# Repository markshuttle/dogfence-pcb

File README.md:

# Dog Fence Indicator & Surge Protection System

**Draft hardware revision: 1.2.1-dev. Reviewed baseline: 1.1.0. File-verified prototype artifacts are authorized; production and field release remain on hold. No upload or order is authorized.**

This repository documents a 4 km DogWatch SmartFence boundary with local DC fault
indicators and GDT surge paths. The implemented 16-part hybrid includes series
indicator branches and negative-voltage output shunts; it is not a qualified
lightning-protection design or completed hardware test report.

[REMEDIATION](REMEDIATION.md) owns the agreed requirements, issue decisions and
revision-specific results. [BOM.csv](pcb/BOM.csv) and the synchronized CAD/local
libraries own PCB population; [ASSEMBLY](pcb/ASSEMBLY.md#reviewed-components)
explains assembly applicability. [MATERIALS](MATERIALS.md#resistor-procurement-and-history)
preserves purchases, cancellations and allocations. A production pre-order is
not an implemented substitution, and prototype results do not qualify another part.

Use the working schematic, PCB, settings/rules and libraries under `pcb/`, not
generated `build/`, backups or `tmp/` copies, as design sources. File verification
does not close the [engineering holds and release gates](REMEDIATION.md#release-gates).

## 1. Deployment Baseline

| Item | Agreed requirement |
| :--- | :--- |
| Stations | **41**, at 0, 100, ..., 4000 m, covering 40 diagnostic spans. The 0 km and 4 km stations are separate boards at the shed. |
| Station types | **36 standard + 5 earth-connected**, retaining earth-connected locations at 0, 1000, 2000, 3000, and 4000 m. Five locations do not imply five independent electrodes. |
| Field equipment | One identical, fully populated board and two external LEDs per station. [MATERIALS](MATERIALS.md#1-station-inventory) owns total requirements, purchases and shortfalls. |
| Initial order | **Five fully assembled JLCPCB boards**, all required SMT and THT parts fitted. No field soldering. Prototype allocation and later production/spares are separate decisions. |
| Fabrication | Readily available **FR-4, two layers, 2 oz / 70 micrometres copper on both F.Cu and B.Cu, ENIG, nominal 1.6 mm finished thickness**. Green soldermask is the quote default, not a new performance qualification. No imposed high-Tg laminate, gold thickness upgrade, or filled-via process. |
| Enclosure | WISKA COMBI 308 with Essentra LCBSBM-6-01A-RT supports and WISKA **OneGel**, subject to assembled fit and process acceptance. Raised installation, not continuous submersion. |
| TEST duty | Nominal 36 V DC, usually one to two hours. **Continuous-safe normal TEST** is required for accidental extended operation; a timer is not the baseline safeguard. Fault/surge safety needs separate evidence. |
| Visibility | ON/OFF distinguishable at **5 m in full daylight**, at the final minimum field current and actual viewing angles. |

[MATERIALS](MATERIALS.md#assembly-and-quantity-allocation) separates field needs
from prototype consumption, the retained reference and spares. A five-board
prototype order is not five proven field spares.

## 2. Operation And Fault Localization

### Hub Contact Matrix

Both physical cable ends return to the shed. The full
[functional matrix](INSTALL.md#functional-matrix) uses **six independent ends**:
TEST feeds Start A/C positive and Start B negative, leaving End A/B/C individually
isolated. Required ties belong on source-side contacts only. No permanent End A/C
strap, opposite-end B return or dual-B negative return is permitted; those
connections defeat the agreed indication. OFF isolates all six ends at the hub,
but is not demonstrated lightning or maintenance isolation.

Follow [INSTALL's switch/source controls](INSTALL.md#switch-and-supply). Exact
switch configuration, DC suitability and global transfer require approval before
physical terminal assignment; extra poles remain unassigned. No direction
selector, automatic core classification or automatic return to RUN is required.

**TEST and OFF disable RF containment.** Provide clear RUN/OFF/TEST and fence-inactive labeling/indication, independent animal containment during testing, and an explicit operator return to RUN. See [INSTALL.md](INSTALL.md) for the controlled operating instructions and [RISKS.md](RISKS.md) for fault/earthing limitations.

### Indication For A Clean Cut

Use [INSTALL's clean-cut truth table](INSTALL.md#clean-cut-indications) for one
cut site with healthy indicators/GDTs and no additional inter-core shorts. The
first applicable state transition identifies the adjacent 100 m span, including
3900-4000 m; exact broken-core classification is not required. For multiple sites,
[repair and repeat TEST](INSTALL.md#repair-and-retest). Mixed open/short faults or
failed indicators/GDTs need separate troubleshooting; not every dark LED proves a cut.

### Station Connections

Three **WAGO 221-613** three-way splices maintain A/B/C cable continuity and provide short 2.5 mm^2 taps to `J_IN`. Normal perimeter current does **not** pass through every PCB's rails; each PCB draws its local indicator current. Surge current through a board is a different design case.

The [implemented circuit](pcb/ELECTRICAL.md#1-implemented-model) has separate
A-to-B and C-to-B one-way indicator branches. D3/D4 are output shunts after
D1/D2, not additional series parts. GDT paths join the core pairs and the separate
EARTH bus. Standard boards retain all parts but leave external `J_EARTH` unwired;
earth-connected stations follow the accepted site design.

RUN parallels the three cores at each transmitter end. The electrical record
preserves the historical parallel-resistance comparison, not RF compatibility
proof. Actual imbalance, faults, capacitance and earth coupling require checks
with the transmitter and receiver; the boards are not demonstrated RF-invisible.

## 3. Electrical Limits And Open Protection Work

Use [ELECTRICAL's named historical comparisons](pcb/ELECTRICAL.md#2-calculated-results)
and [DESIGN_BOUNDS](pcb/DESIGN_BOUNDS.md) for the current population's
cable/tolerance, leakage, power and fault screens. They are conditional models,
not measurements, enforced source limits, an exhaustive brightness minimum or
thermal qualification. The source/test commands and assumptions travel with those
records; do not copy retired-part values into current operating limits.

- Use **one TEST supply and one disconnected spare**, never interconnected
  supplies. Verify the actual unit and qualified settings under
  [INSTALL](INSTALL.md#switch-and-supply); a larger PSU does not coordinate faults.
- Negative shunts are not forward pulse-current regulators or reversed-lead
  immunity. Reverse recovery is not forward-clamp response. Ordinary RF,
  switching and nearby-lightning behavior remain unqualified.
- Cable-limited faults may not clear the fuse promptly. Powered-GDT recovery is
  unresolved, not an observed latched failure; conditional load lines do not
  predict extinction. Indicator resistors/shunts do not protect upstream GDT paths.
- Resistor wattage and SMT construction do not prove cool OneGel operation.
  Manufacturer mounting/rating transfer and actual chip/pad/PCB/material-interface
  temperatures require separate qualification; retired-part pulse/thermal data do
  not transfer. Continuous-safe normal TEST remains mandatory, without a timer.
- DC sparkover is not transient clamp voltage. Component impulse ratings,
  paralleled pins and heavy copper do not establish assembled surge/current,
  equal-sharing, direct-strike or lifetime ratings.

The [accepted risk boundaries](REMEDIATION.md#agreed-requirements) allow LED
damage from accidental installation polarity errors and rebuilding after a direct
strike, not all ordinary/nearby transient damage. Maintain the
[whole-boundary cattle-fence prohibition](INSTALL.md#cattle-fence-prohibition);
the withdrawn exposure is not qualified safe. [ACCEPTANCE](ACCEPTANCE.md) defines
the unperformed hardware tests; [RISKS](RISKS.md) explains their consequences.

## 4. Hardware Component Selection & Specifications

Use [BOM.csv](pcb/BOM.csv) and [Reviewed Components](pcb/ASSEMBLY.md#reviewed-components)
for the exact population, sourcing identities and assembly requirements. Detailed
component electrical ratings remain in [ELECTRICAL](pcb/ELECTRICAL.md#1-implemented-model);
reviewed drawings, maximum dimensions and rating conditions remain in the
controlled assembly/evidence notes. A C-code is not footprint or stock allocation
approval. The external indicator's limits, polarity, mounting and visibility
requirements are in [LED.md](LED.md).

[MATERIALS](MATERIALS.md#resistor-procurement-and-history) owns cancelled,
superseded and rejected selections. They are not substitutions or a second active
BOM. Sourcing parity does not establish job allocation; unresolved External rows
still block both publication modes under [AGENTS' sourcing rules](AGENTS.md#3-verification-and-publication).

## 5. Unapproved Alternatives

Retain these earlier sourcing suggestions for investigation, **not as approved upgrades or drop-ins**. No purchase, footprint fit, higher assembled surge capability, or lifetime benefit is established by this list. Differences in electrode configuration, body, lead diameter, pin mapping, RF loading, and thermal/pulse behavior may require redesign and new qualification.

| Intended references | Previously suggested alternatives |
| :--- | :--- |
| D1, D2 | Vishay 1N4007GP-E3/54 |
| R1, R2 | Vishay PR02000202201JA100, historical PR02 suggestion; both it and the former 1% FA100 selection are **retired, not the selected 2512 SMT part** |
| GDT_AB, GDT_BC | Littelfuse SH470 |
| GDT_AC | Bourns 2027-47-BLF or Littelfuse CG2-470L |
| Earth GDTs | Littelfuse SL1021A470R |
| J_IN, J_EARTH | Phoenix Contact 1731734, GMKDS 3/ 3-7,62 |
| LED terminals | Phoenix Contact 1715721, MKDS 1,5/ 2-5,08 |
| External LED | APEM Q14P5BXXHG02E, discussed in LED.md |

A higher resistor wattage does not reduce heat at the same resistance/current. A larger LED bezel does not prove better daylight contrast. Global sourcing/private inventory is an option only after engineering approval and a supplier quote; it is not a guaranteed route to stock or a fixed lead time.

## 6. PCB And Assembly Constraints

**Read [ASSEMBLY's Physical Guardrails](pcb/ASSEMBLY.md#physical-guardrails)
before changing geometry or process.** It owns the complete outline/mount,
copper/via, isolation, polarity, placement, land, forming and tolerance inventories.
Preserve protected geometry and distinct local LED mappings; do not narrow copper,
fold branches, add vias or trim courtyards to conceal an assembly problem.

The **2026-09-14 user-approved change** makes GDT_AC the same top-side Ruilon
SMT part as GDT_AB/BC and carries the B crossing on the rear layer. A/C main
rails remain 3.20 mm on both faces; the rear B main rail is **exactly 6.00 mm**,
with the approved front-B stop and minimal rear-return move controlled in
ASSEMBLY. The new **>=3.00 mm A/B/C inter-core copper rule is B.Cu-only**, not
a blanket front-layer rule. GDT_AC's axial overpass and two insertion holes are
retired; only the three earth GDTs still require lead forming. The board
dielectric at the crossing is not qualified impulse insulation. Circuit
connectivity, RUN/TEST operation and the distinct LED mappings are unchanged.

The subsequently approved **1.2.1-dev westward spacing change** relocates the
nine rail vias and three SMT GDTs and shortens front B. The
[current spacing controls](pcb/ASSEMBLY.md#smt-via-relocation) require **>=3.00 mm
between unlike-net pads of different GDTs and between AC pads and front B
copper**, with **3.20 mm nominal minimum**. Each tube's internal land/copper
gaps are a separate scope; neither the new spacing nor DRC proves flashover immunity.

The approved **2 mm east board extension**, still **1.2.1-dev**, makes the
outline **65 x 56 mm** and moves H2/H4 east without moving J_EARTH or functional
copper. [J_EARTH's edge-clearance controls](pcb/ASSEMBLY.md#earth-terminal-edge-clearance)
own the nominal-versus-budgeted body/pose and courtyard margins; neither is
supplier-tolerance or measured-fit approval.

The [retained resistor lands](pcb/ASSEMBLY.md#2512-smt-resistors) are an
alternative to the manufacturer's recommendation, not an exact-fit approval.
Actual parts, stencil/solder process, earth-GDT forming, edge clearance and
enclosure/support fit remain separate acceptance tasks. Source stackup arithmetic is not a finished
thickness guarantee; ENIG is not a hermetic seal. Use the controlled notes and
[ORDERING](ORDERING.md#3-hole-via-and-solder-process) for the actual handoff.

### Via and Component Hole DFM

**Policy updated 2026-09-07. Selected standard process: UNTENTED both sides, no fill/plug/cap, ENIG.** Source openings are nominal 1.80 mm with no via paste; no special 1.00 mm filling or reliable tenting is assumed. Recheck each actual order's processed data and assembly process. References: [JLCPCB capabilities](https://jlcpcb.com/capabilities/pcb-capabilities), [via covering](https://jlcpcb.com/help/article/pcb-via-covering), and [via versus component-hole tolerances](https://jlcpcb.com/help/article/difference-and-tolerance-explanation-between-via-and-pad-holes).

The following limits concern the **hole**, not its copper pad:

| Process | Published guidance | Consequence for the protected 1.0 mm holes |
| :--- | :--- | :--- |
| **Untented, selected** | Standard process; exposed copper receives ENIG. | No seal. Inspect solder ingress/beads and environmental protection. |
| Tented | Ideally at most 0.4 mm; normal coverage guidance at most 0.5 mm. | Larger holes are not guaranteed covered. A KiCad tenting flag is not proof. |
| Soldermask plugged | At most 0.5 mm, no mask openings on either side, at least 0.35 mm process clearance from other mask openings/pads. | Outside the normal limit. Ink plugging is not filled-and-capped via-in-pad processing. |
| Filled and capped | Detailed guide recommends at most 0.5 mm; capability table lists 0.15-0.55 mm. Resolve the applicable limit with CAM. | 1.0 mm exceeds both ranges; any exception needs written process acceptance. |

- Preserve **all 14 stitching vias at 1.0 mm drill / 1.8 mm pad** and the protected copper. Fix surrounding soldering geometry or seek an approved process/layout solution; do not delete or shrink vias to fit a covering option.
- Inspect full drill circles and exposed annuli against actual `F.Mask`, `B.Mask`, and `F.Paste`, then the processed mask/stencil. [ASSEMBLY's SMT/via inventory](pcb/ASSEMBLY.md#smt-via-relocation) records the corrected aperture gaps and selected metric lands; the drawing discrepancy and actual solder-volume/profile acceptance remain held. Adjacent same-net rail-via mask circles intentionally overlap, but no component paste/mask aperture is excused over a via hole.
- Identify treatment by **coordinates and hole function**, never diameter alone. Legacy resistor/diode and GDT_AC insertion holes are retired. All retained connector/earth-GDT insertion holes remain open. Ordinary via diameters may be adjusted in CAM; check that no protected nominal drill was reduced. No fill is requested.
- **70 micrometres of exterior copper is not 70 micrometres of barrel plating.** JLCPCB's published 18 micrometres average hole plating is not a guaranteed minimum in every barrel. Agree any finished minimum used in current/surge calculations separately. Nonconductive fill adds no conductive cross-section.
- Tenting, plugging, opacity, or gel encapsulation does not prove hermetic sealing, freeze-thaw immunity, or an assembled ingress rating.

Use **component PTH pads**, never ordinary vias, for lead insertion. Record the exact manufacturer/MPN, drawing revision, maximum finished lead dimensions, pitch, proposed hole, and assembly allowance. For round holes:

```text
Round pin envelope       = maximum finished lead diameter
Rectangular pin envelope = sqrt(maximum_width^2 + maximum_thickness^2)
nominal finished hole - 0.08 mm >= maximum pin envelope + 0.10 mm
```

The last line uses JLCPCB's ordinary component-hole **+0.13/-0.08 mm** tolerance and the project's starting **0.10 mm diametral allowance after tolerance**. Increase the allowance when required; also account for pin-pitch, hole-position, and forming tolerances, particularly rigid connectors. This is stricter than simply adding 0.10 mm to a nominal pin. Do not assume press-fit tolerances for this order.

The exact [SMA lands/polarity](pcb/ASSEMBLY.md#indicator-sma-and-resistor-assembly),
[resistor lands](pcb/ASSEMBLY.md#2512-smt-resistors) and
[component hole/pad/pin schedule](pcb/ASSEMBLY.md#hole-fit-evidence) are controlled
in ASSEMBLY. Diodes, resistors and all three inter-core GDTs are SMT, not insertion
or axial-forming parts. Allocated THT parts must pass free-insertion, earth-GDT
forming/standoff and solder inspection with separate position/pattern allowances. Supplier CAD or nominal
pitch is not actual lot acceptance.

After drill changes, recheck pad sizes, hole/copper spacing, edge clearances and **at least 0.254 mm nominal component PTH annular ring for two-layer 2 oz fabrication**. Generic via-ring rules do not establish component-pad compliance. Finished-ring acceptance also requires hole and registration tolerances. Resolve fit in CAD, not by forced insertion or reaming plated boards.

DRC alone cannot close hole-fit, solder-wicking, body/forming, or process approval. Record the accepted evidence in the controlled assembly notes, regenerate the production outputs, and inspect the final processed files.

## 7. Enclosure, Cable And Site

Follow [INSTALL's materials/site requirements](INSTALL.md#materials-and-site),
[workshop dry-fit](INSTALL.md#workshop-assembly) and
[gel/service procedure](INSTALL.md#gel-and-service). The coastal, wet and partly
sunlit route requires assembled thermal/environmental qualification, not reliance
on component IP or temperature labels. OneGel is single-component/no mixing;
its conflicting published process/temperature fields and missing thermal data
remain unresolved in [ENVIRONMENT_EVIDENCE](pcb/ENVIRONMENT_EVIDENCE.md).

Cable identity and red/black/plain-green colours are settled; supplied-lot,
UV/wet-conduit and impulse applicability still need evidence. Label A/B/C
end-to-end: plain green is not PE, and **green/yellow is never an active core**.
Keep the boundary electrically separate from supporting fence wires and inspect
and maintain the [whole-boundary cattle-fence prohibition](INSTALL.md#cattle-fence-prohibition).

A qualified installer must approve the site-specific PE/electrode/OEM protection
arrangement, including the proposed shared shed earth. Do not directly earth a
core, switch PE or invent unbonded rods or a DC-negative earth bond. Inventory is
not an approved discharge-path design. Apply [INSTALL's safety controls](INSTALL.md#safety-first).

## 8. Verification And Release

Use the headless environment and full
[verification/publication workflow](AGENTS.md#3-verification-and-publication).
Native DRC/ERC, parity, geometry, population and exported artifacts are checked
against a complete snapshot. All errors and unreviewed diagnostics block; narrow
reviewed warnings remain visible. Tested KiCad is **9.0.7**, not an unverified
7/8 compatibility claim.

```bash
make check
make prototype
```

`make check` verifies without publication and refreshes the draft CPL only after
all file/artifact checks pass. `make prototype` / `make gerbers` may publish
**FILE-VERIFIED PROTOTYPE ONLY** with all five ledger holds deferred, not closed.
Production targets retain their holds and win mixed goals; unresolved External
sourcing blocks both modes. The [east-extension handoff](REMEDIATION.md#east-board-extension)
controls current verification status and the matching source/controlled-note snapshot.

The earlier [westward-spacing checks](REMEDIATION.md#westward-gdt-spacing) and
SMT AC/rear-B publication remain historical evidence for their recorded inputs.
They do not verify the east extension or changed controlled notes, even where
the **1.2.1-dev** identifier is unchanged.

Require matching `build/status.json` and `build/manifest.json` with validated
revision/source/artifact hashes and **status=prototype, mode=prototype**, or
production **status=verified, mode=build**. Shared filenames alone prove nothing.
New attempts quarantine old outputs; run cleanup separately and preserve evidence.

[ORDERING's artifact guide](ORDERING.md#1-before-upload) describes Gerbers,
BOM/CPL, bare-board FlyTest and assembly aids. Generated mode/hold notices travel
inside both ZIPs; the seven controlled notes accompany the full release directory,
not the ZIPs alone. Never hand-edit artifacts or correct signed Y with `abs(Y)`.
Obtain separate processed CAM/stencil and parts-placement/assembly approvals.

The [release-gate definitions](REMEDIATION.md#release-gates) keep Gate P separate
from original A/B/C production/field holds. Supplier part/fit/forming, allocation,
panel/process and CAM/placement remain order tasks. Enclosure dry-fit and
prototype-dependent tests follow receipt, not as prerequisites to prototype files.
Neither file generation nor basic five-board tests authorize upload, an order,
containment/protection use or full rollout.

## 9. Documentation Map

| Document | Role |
| :--- | :--- |
| [REMEDIATION.md](REMEDIATION.md) | Agreed requirements, issue/evidence register, gates and session handoff. |
| [AGENTS.md](AGENTS.md) | Headless tooling, staging, mandatory guardrail reads and documentation maintenance. |
| [INSTALL.md](INSTALL.md), [RISKS.md](RISKS.md), [ACCEPTANCE.md](ACCEPTANCE.md) | Operating, risk and qualification procedures, synchronized by their owners with the final circuit. |
| [ORDERING.md](ORDERING.md), [MATERIALS.md](MATERIALS.md), [LED.md](LED.md) | Quote/approval workflow, procurement ledger, indicator limits and visibility target. |
| [REVIEW.md](REVIEW.md) | Reusable read-only audit brief, not a completed review or sign-off. |
| [ELECTRICAL](pcb/ELECTRICAL.md), [ASSEMBLY](pcb/ASSEMBLY.md), [DESIGN_BOUNDS](pcb/DESIGN_BOUNDS.md) | Circuit/model interpretation, physical/component controls and current parametric screens. |
| [DFM evidence](pcb/DFM_EVIDENCE.md), [environment evidence](pcb/ENVIRONMENT_EVIDENCE.md), [LED research](pcb/LED_PROTECTION_RESEARCH.md), [source research](pcb/SOURCE_PROTECTION_RESEARCH.md) | Manufacturer evidence, named historical investigations and later applicability corrections; not selected circuits or approvals. |
| [Makefile](Makefile), `pcb/pcb.kicad_sch`, `pcb/pcb.kicad_pcb`, `pcb/pcb.kicad_pro` | Build implementation and authoritative design/project sources, together with applicable rules and local libraries. |

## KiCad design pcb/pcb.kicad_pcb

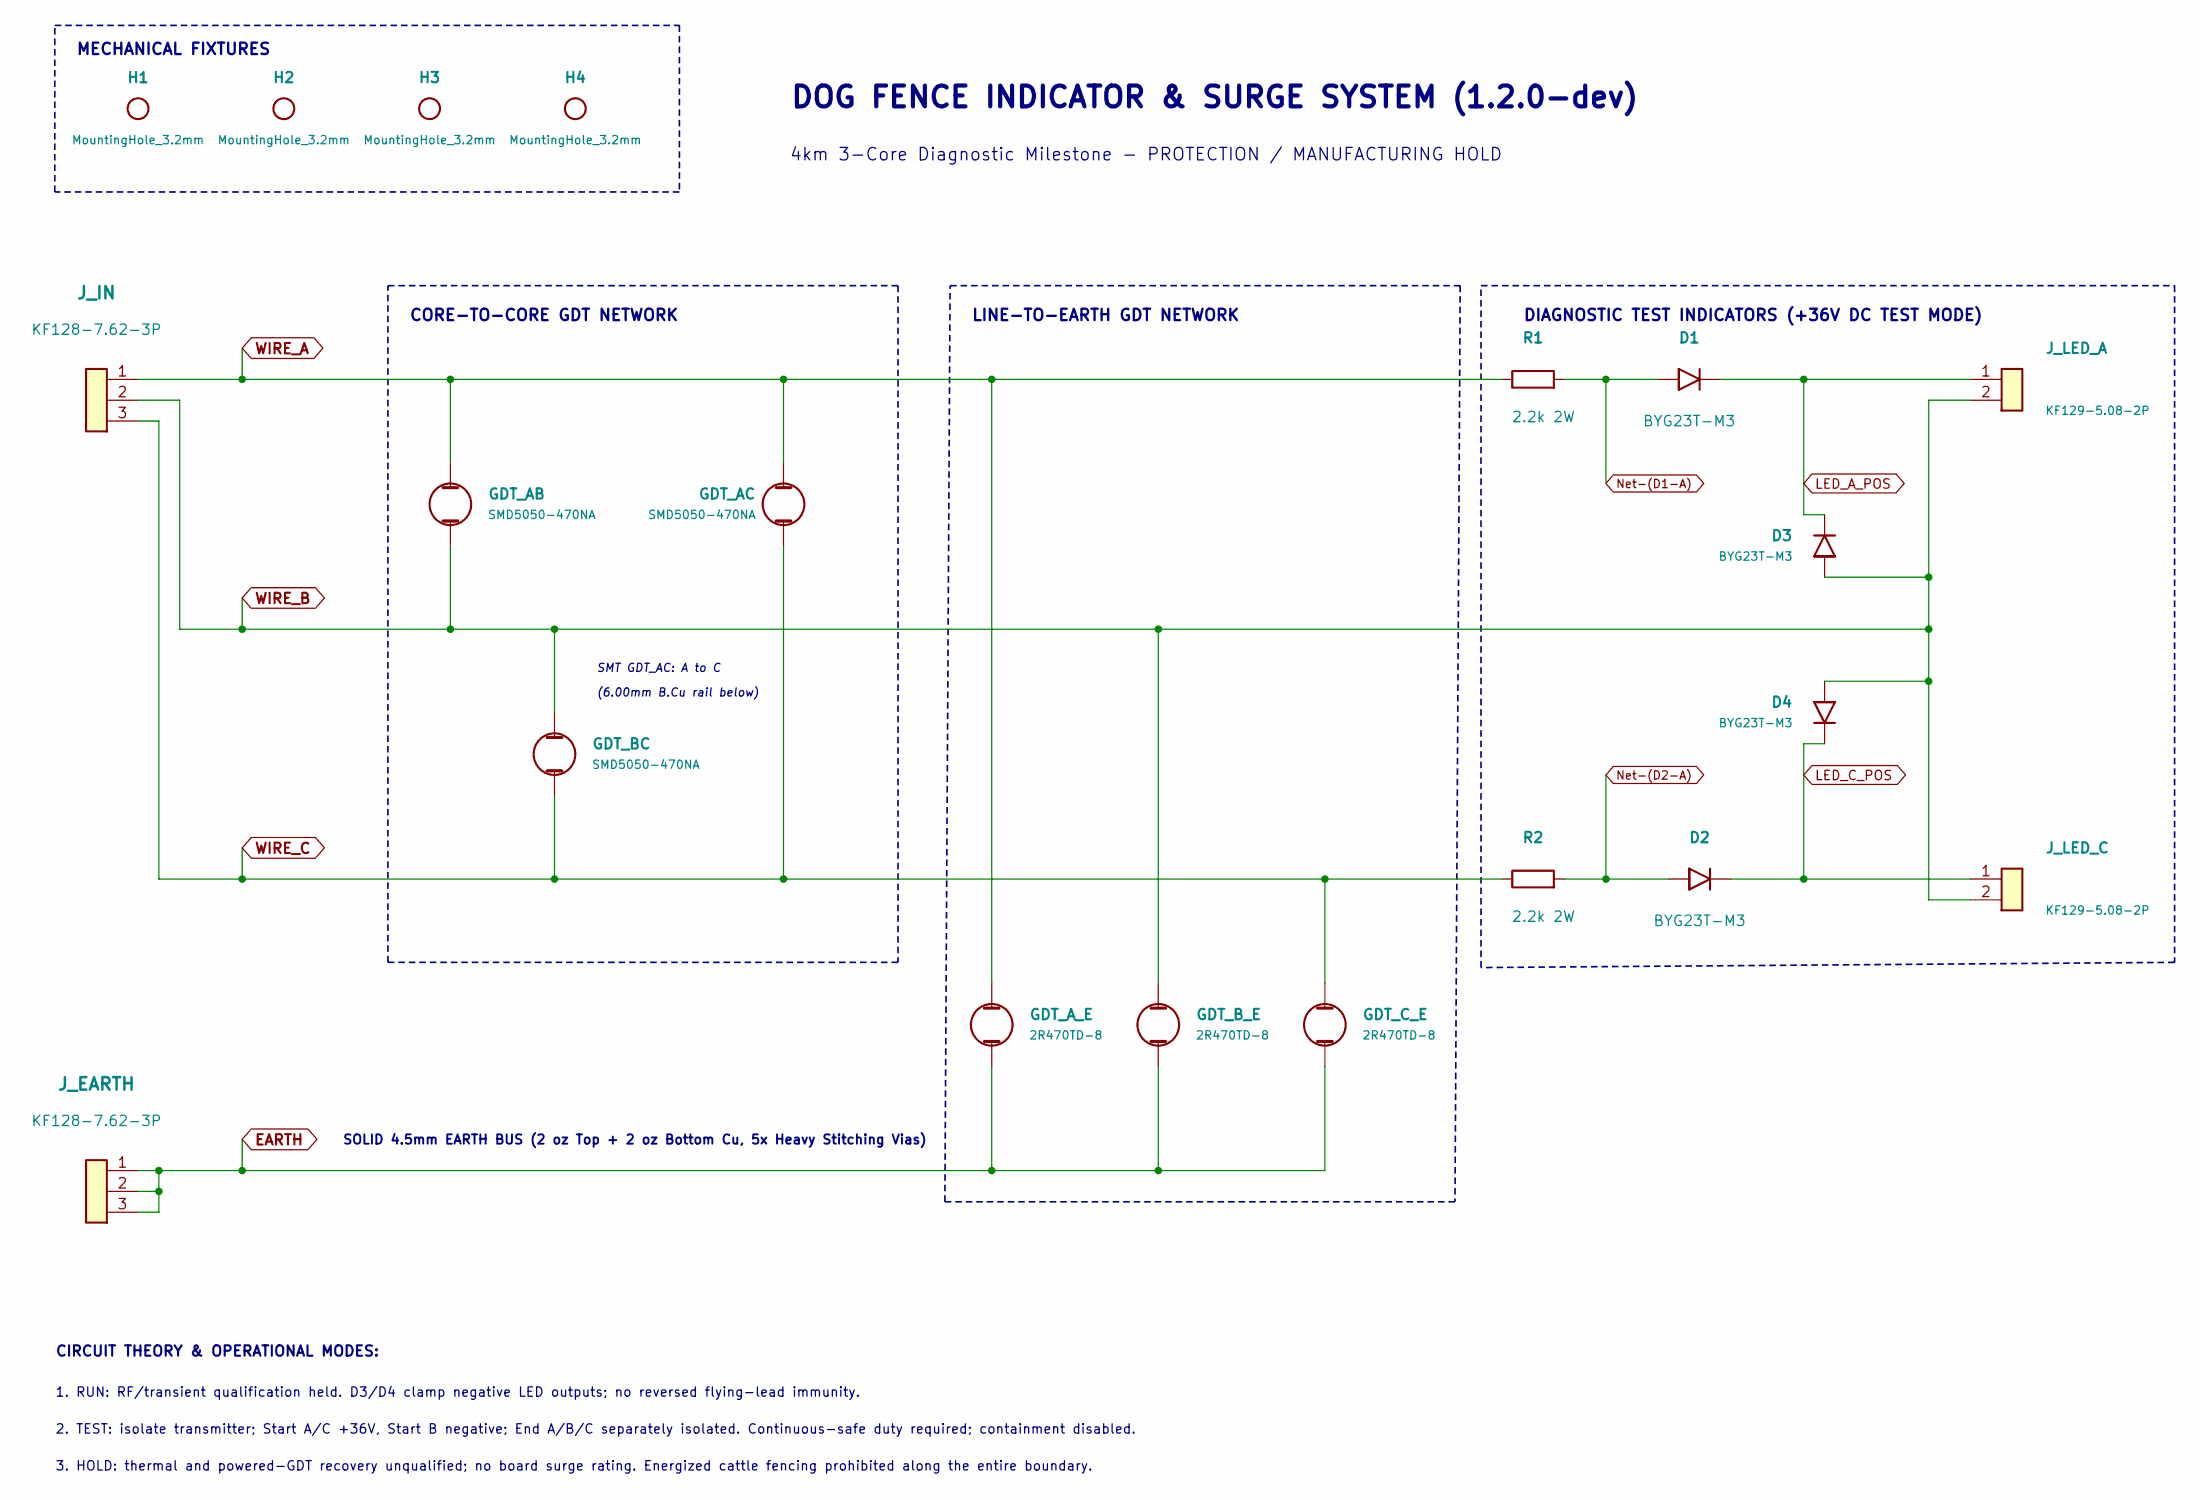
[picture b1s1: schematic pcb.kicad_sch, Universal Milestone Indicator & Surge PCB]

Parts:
D1, D2, D3, D4: BYG23T-M3; BYG23T_SMA_K_Right; MPN BYG23T-M3/TR; LCSC C145454
GDT_AB: SMD5050-470NA; MPN SMD5050-470NA; LCSC C39692533
GDT_AC: SMD5050-470NA; MPN SMD5050-470NA; LCSC C39692533
GDT_A_E: 2R470TD-8; 2R470TD-8_P15.24mm; MPN 2R470TD-8; LCSC C2836978
GDT_BC: SMD5050-470NA; MPN SMD5050-470NA; LCSC C39692533
GDT_B_E: 2R470TD-8; 2R470TD-8_P15.24mm; MPN 2R470TD-8; LCSC C2836978
GDT_C_E: 2R470TD-8; 2R470TD-8_P15.24mm; MPN 2R470TD-8; LCSC C2836978
H1, H2, H3, H4: MountingHole_3.2mm
J_EARTH: KF128-7.62-3P; KF128_7.62_3P_Earth; MPN KF128-7.62-3P; LCSC C474957
J_IN: KF128-7.62-3P; KF128_7.62_3P_Input; MPN KF128-7.62-3P; LCSC C474957
J_LED_A: KF129-5.08-2P; KF129_5.08_2P_LED_A; MPN KF129-5.08-2P; LCSC C475092
J_LED_C: KF129-5.08-2P; KF129_5.08_2P_LED_C; MPN KF129-5.08-2P; LCSC C475092
R1, R2: 2.2k 2W; R_2512_6332Metric; MPN 35212K2FT; LCSC C4129105

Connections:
EARTH: GDT_A_E.2, GDT_B_E.2, GDT_C_E.2, J_EARTH.1, J_EARTH.2, J_EARTH.3
LED_A_POS: D1.1 (K), D3.1 (K), J_LED_A.1
LED_C_POS: D2.1 (K), D4.1 (K), J_LED_C.1
unnamed: D1.2 (A), R1.2
unnamed: D2.2 (A), R2.2
WIRE_A: GDT_AB.1, GDT_AC.1, GDT_A_E.1, J_IN.1, R1.1
WIRE_B: D3.2 (A), D4.2 (A), GDT_AB.2, GDT_BC.1, GDT_B_E.1, J_IN.2, J_LED_A.2, J_LED_C.2
WIRE_C: GDT_AC.2, GDT_BC.2, GDT_C_E.1, J_IN.3, R2.1

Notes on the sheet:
MECHANICAL FIXTURES
CORE-TO-CORE GDT NETWORK
LINE-TO-EARTH GDT NETWORK
DIAGNOSTIC TEST INDICATORS (+36V DC TEST MODE)
DOG FENCE INDICATOR & SURGE SYSTEM (1.2.0-dev)
4km 3-Core Diagnostic Milestone - PROTECTION / MANUFACTURING HOLD
CIRCUIT THEORY & OPERATIONAL MODES:
SMT GDT_AC: A to C
SOLID 4.5mm EARTH BUS (2 oz Top + 2 oz Bottom Cu, 5x Heavy Stitching Vias)
1. RUN: RF/transient qualification held. D3/D4 clamp negative LED outputs; no reversed flying-lead immunity.
2. TEST: isolate transmitter; Start A/C +36V, Start B negative; End A/B/C separately isolated. Continuous-safe duty required; containment disabled.
3. HOLD: thermal and powered-GDT recovery unqualified; no board surge rating. Energized cattle fencing prohibited along the entire boundary.
(6.00mm B.Cu rail below)

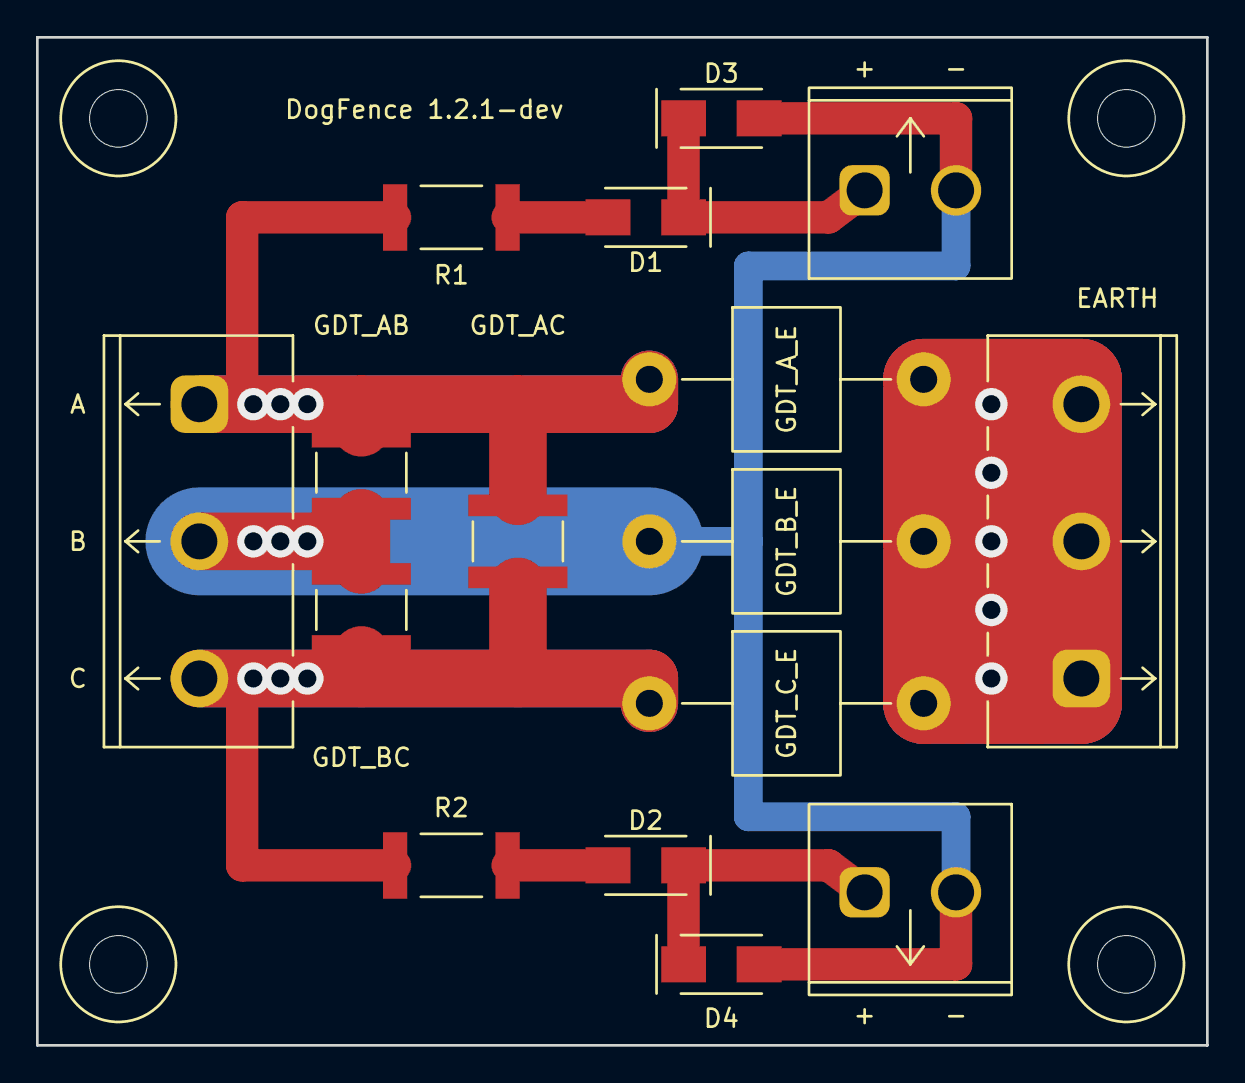
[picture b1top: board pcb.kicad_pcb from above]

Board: 2 copper layers, 65.0 x 56.0 mm, 20 parts (0 on the bottom side), 8 nets.

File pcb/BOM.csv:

Comment,Designator,Footprint,LCSC Part #,MPN,Manufacturer,Sourcing,Sourcing Reference
"KF128-7.62-3P",J_IN,"DogFence:KF128_7.62_3P_Input",C474957,"KF128-7.62-3P","Cixi Kefa Elec",LCSC,
"KF128-7.62-3P",J_EARTH,"DogFence:KF128_7.62_3P_Earth",C474957,"KF128-7.62-3P","Cixi Kefa Elec",LCSC,
"KF129-5.08-2P",J_LED_A,"DogFence:KF129_5.08_2P_LED_A",C475092,"KF129-5.08-2P","Cixi Kefa Elec",LCSC,
"KF129-5.08-2P",J_LED_C,"DogFence:KF129_5.08_2P_LED_C",C475092,"KF129-5.08-2P","Cixi Kefa Elec",LCSC,
"2.2k 2W",R1,"DogFence:R_2512_6332Metric",C4129105,"35212K2FT","TE Connectivity",LCSC,
"2.2k 2W",R2,"DogFence:R_2512_6332Metric",C4129105,"35212K2FT","TE Connectivity",LCSC,
"BYG23T-M3",D1,"DogFence:BYG23T_SMA_K_Right",C145454,"BYG23T-M3/TR","Vishay General Semiconductor",LCSC,
"BYG23T-M3",D2,"DogFence:BYG23T_SMA_K_Right",C145454,"BYG23T-M3/TR","Vishay General Semiconductor",LCSC,
"BYG23T-M3",D3,"DogFence:BYG23T_SMA_K_Right",C145454,"BYG23T-M3/TR","Vishay General Semiconductor",LCSC,
"BYG23T-M3",D4,"DogFence:BYG23T_SMA_K_Right",C145454,"BYG23T-M3/TR","Vishay General Semiconductor",LCSC,
"SMD5050-470NA",GDT_AB,"DogFence:SMD5050-470NA",C39692533,"SMD5050-470NA","Ruilon",LCSC,
"SMD5050-470NA",GDT_BC,"DogFence:SMD5050-470NA",C39692533,"SMD5050-470NA","Ruilon",LCSC,
"SMD5050-470NA",GDT_AC,"DogFence:SMD5050-470NA",C39692533,"SMD5050-470NA","Ruilon",LCSC,
"2R470TD-8",GDT_A_E,"DogFence:2R470TD-8_P15.24mm",C2836978,"2R470TD-8","Ruilon",LCSC,
"2R470TD-8",GDT_B_E,"DogFence:2R470TD-8_P15.24mm",C2836978,"2R470TD-8","Ruilon",LCSC,
"2R470TD-8",GDT_C_E,"DogFence:2R470TD-8_P15.24mm",C2836978,"2R470TD-8","Ruilon",LCSC,
